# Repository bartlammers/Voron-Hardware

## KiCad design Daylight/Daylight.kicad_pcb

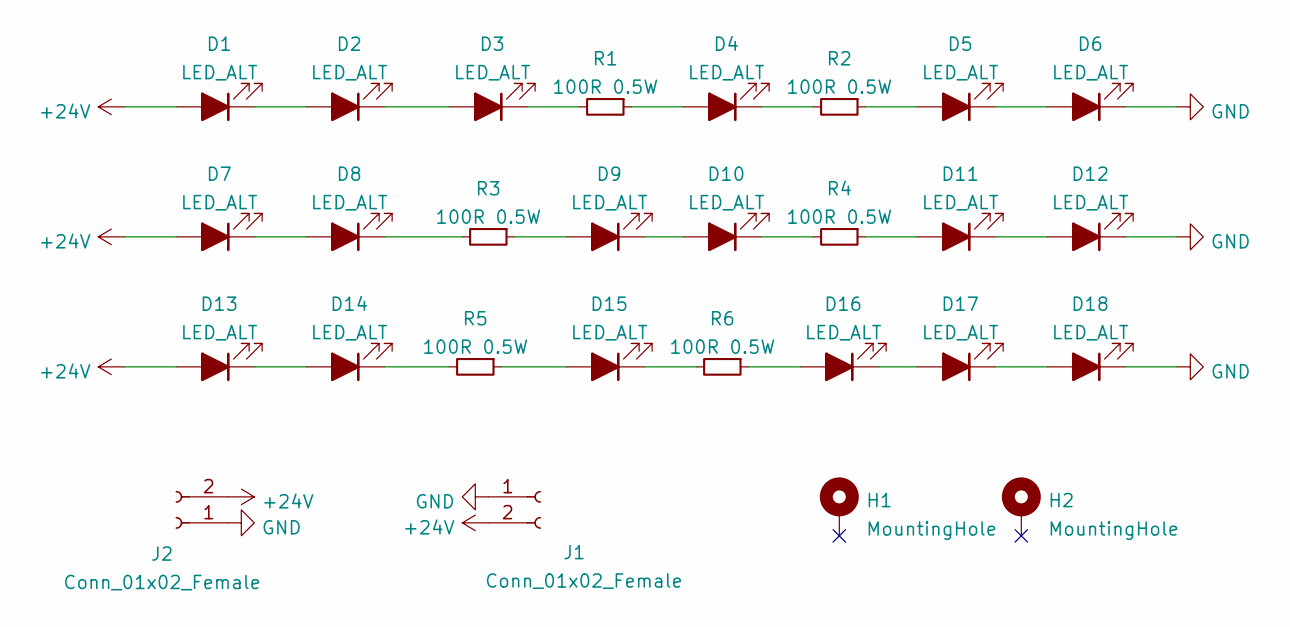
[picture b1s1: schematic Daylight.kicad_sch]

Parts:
D1, D2, D3, D4, D5, D6, D7, D8, D9, D10, D11, D12, D13, D14, D15, D16, D17, D18: LED_ALT; LED_PLCC_2835_Handsoldering_flipped; LCSC C182223
H1, H2: MountingHole; MountingHole_3.2mm_M3_Pad_Via
J1: Conn_01x02_Female; PinHeader_1x02_P2.54mm_Horizontal_mirrored
J2: Conn_01x02_Female; PinHeader_1x02_P2.54mm_Horizontal
R1, R2, R3, R4, R5, R6: 100R 0.5W; R_1210_3225Metric_Pad1.30x2.65mm_HandSolder; LCSC C137089

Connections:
+24V: D1.2 (A), D7.2 (A), D13.2 (A), J1.2, J2.2
GND: D6.1 (K), D12.1 (K), D18.1 (K), J1.1, J2.1
unnamed: D1.1 (K), D2.2 (A)
unnamed: D2.1 (K), D3.2 (A)
unnamed: D3.1 (K), R1.2
unnamed: D4.1 (K), R2.2
unnamed: D4.2 (A), R1.1
unnamed: D5.1 (K), D6.2 (A)
unnamed: D5.2 (A), R2.1
unnamed: D7.1 (K), D8.2 (A)
unnamed: D8.1 (K), R3.2
unnamed: D9.2 (A), R3.1
unnamed: D10.1 (K), R4.2
unnamed: D9.1 (K), D10.2 (A)
unnamed: D11.1 (K), D12.2 (A)
unnamed: D11.2 (A), R4.1
unnamed: D13.1 (K), D14.2 (A)
unnamed: D14.1 (K), R5.2
unnamed: D15.1 (K), R6.2
unnamed: D15.2 (A), R5.1
unnamed: D16.1 (K), D17.2 (A)
unnamed: D16.2 (A), R6.1
unnamed: D17.1 (K), D18.2 (A)

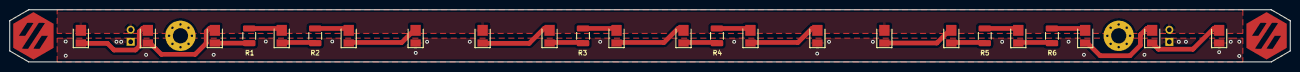
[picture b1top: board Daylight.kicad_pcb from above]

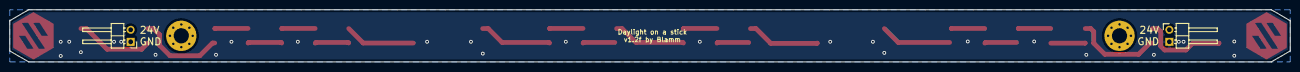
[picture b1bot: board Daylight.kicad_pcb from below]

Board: 2 copper layers, 270.0 x 11.0 mm, 28 parts (2 on the bottom side), 23 nets.

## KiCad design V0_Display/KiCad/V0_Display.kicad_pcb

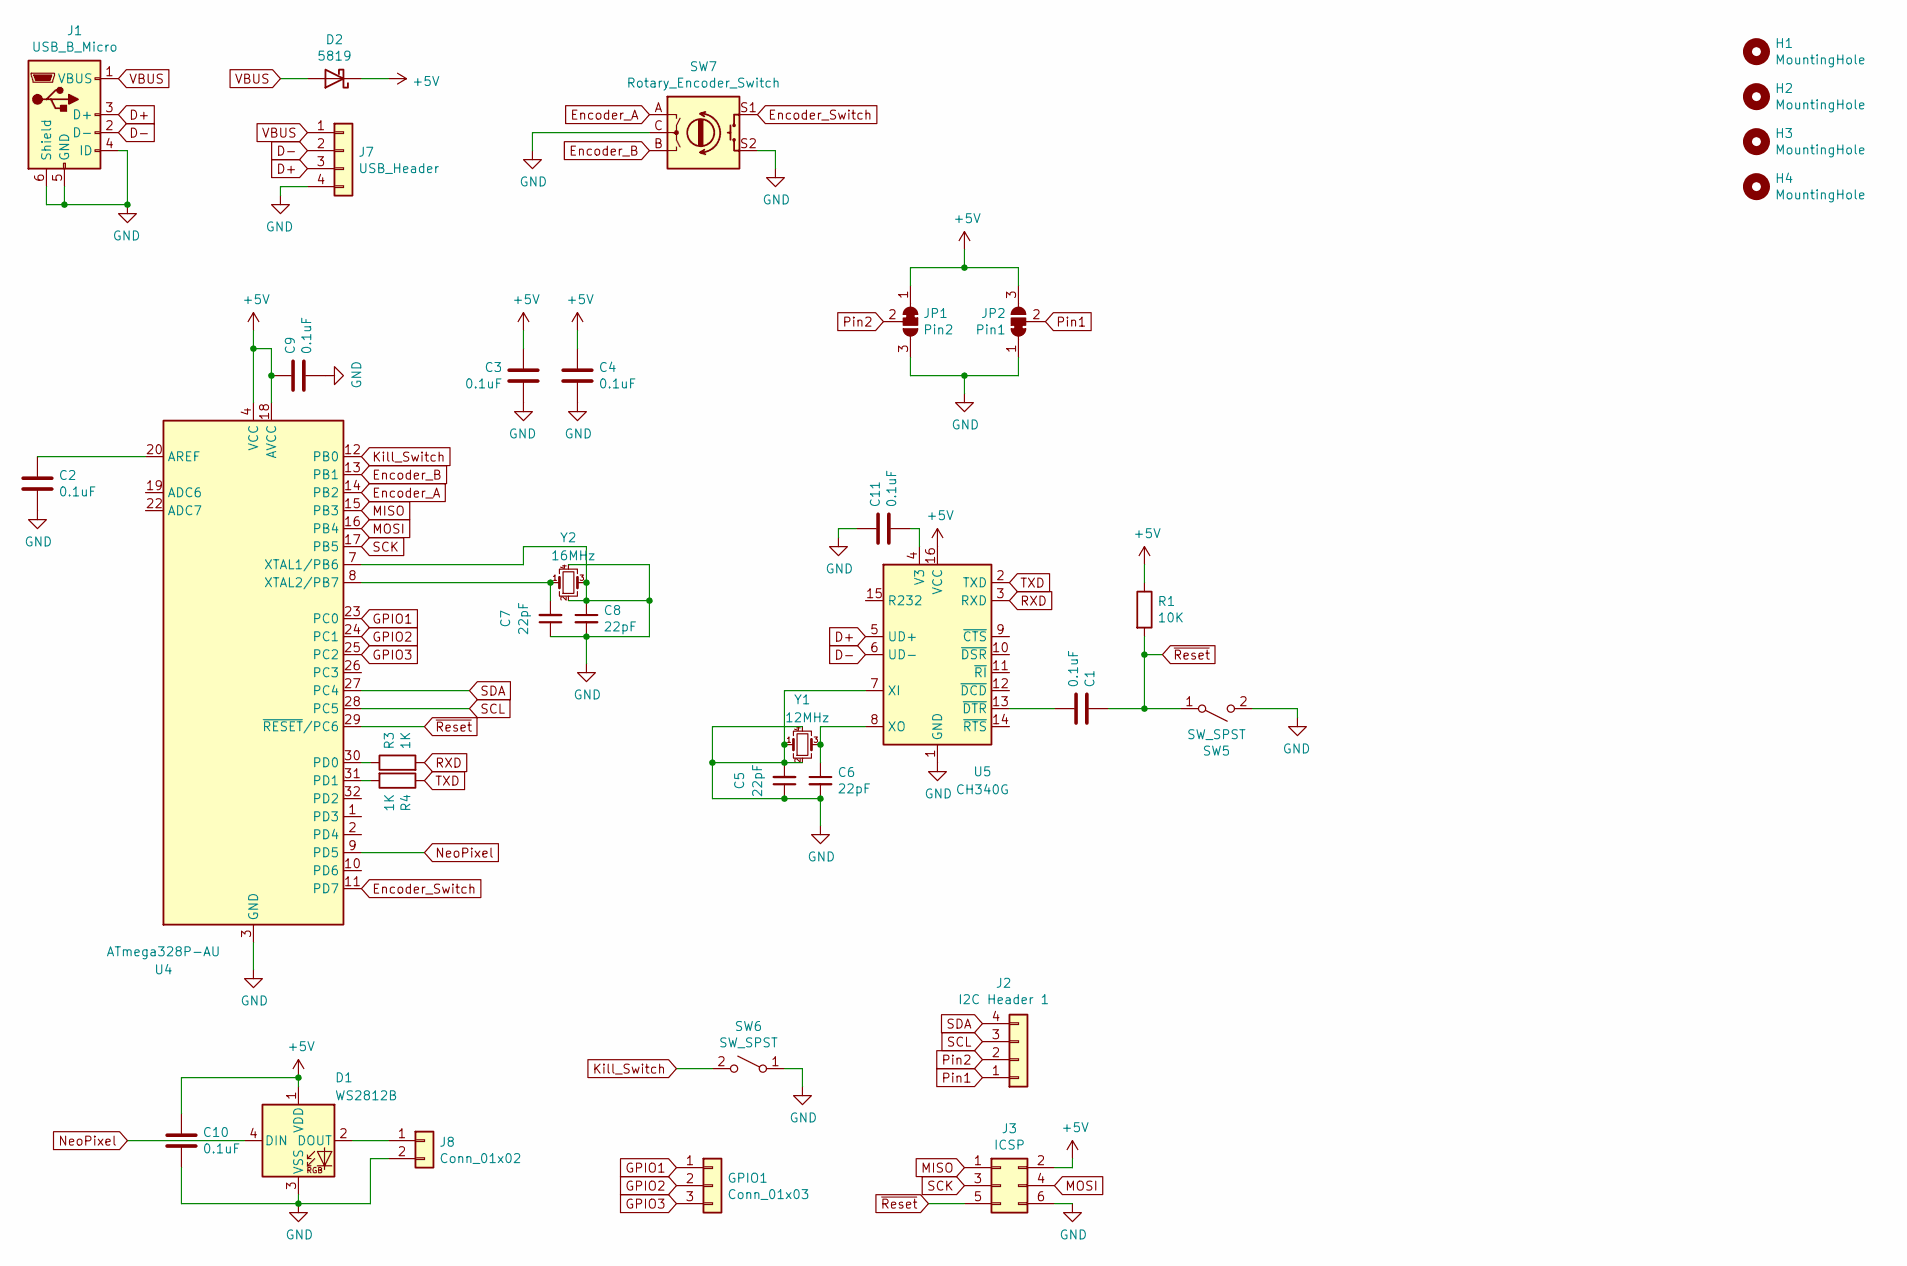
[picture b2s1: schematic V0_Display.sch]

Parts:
C1, C2, C3, C4, C9, C10, C11: 0.1uF; C_0603_1608Metric; LCSC C14663
C5, C6, C7, C8: 22pF; C_0603_1608Metric; LCSC C1653
D1: WS2812B; LED_WS2812B_PLCC4_5.0x5.0mm_P3.2mm
D2: 5819; D_SOD-123; LCSC C8598
GPIO1: Conn_01x03; PinHeader_1x03_P2.54mm_Vertical
H1, H2, H3, H4: MountingHole; MountingHole_3.2mm_M3
J1: USB_B_Micro; MolexVertical&Horizontal_MicroB
J2: I2C Header 1; 1pt3in_OLED
J3: ICSP; PinHeader_2x03_P2.54mm_Vertical
J7: USB_Header; PinHeader_1x04_P2.54mm_Vertical
J8: Conn_01x02; PinHeader_1x02_P2.54mm_Vertical
JP1: Pin2; SolderJumper-3_P1.3mm_Bridged12_Pad1.0x1.5mm
JP2: Pin1; SolderJumper-3_P1.3mm_Bridged12_Pad1.0x1.5mm
R1: 10K; R_0805_2012Metric; LCSC C17414
R3, R4: 1K; R_0805_2012Metric; LCSC C17513
SW5, SW6: SW_SPST; SW_PUSH_6mm
SW7: Rotary_Encoder_Switch; EN11_Encoder
U4: ATmega328P-AU; TQFP-32_7x7mm_P0.8mm; LCSC C14877
U5: CH340G; SOIC-16_3.9x9.9mm_P1.27mm; LCSC C14267
Y1: 12MHz; Crystal_SMD_3225-4Pin_3.2x2.5mm; LCSC C9002
Y2: 16MHz; Crystal_SMD_3225-4Pin_3.2x2.5mm; LCSC C13738

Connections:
+5V: C3.2, C4.1, C9.1, C10.1, D1.1 (VDD), D2.1 (K), J3.2, JP1.1 (A), JP2.3 (B), R1.1, U4.4 (VCC), U4.6 (VCC), U4.18 (AVCC), U5.16 (VCC)
D+: J1.3 (D+), J7.3, U5.5 (UD+)
D-: J1.2 (D-), J7.2, U5.6 (UD-)
Encoder_A: SW7.A, U4.14 (PB2)
Encoder_B: SW7.B, U4.13 (PB1)
Encoder_Switch: SW7.S1, U4.11 (PD7)
GND: C2.2, C3.1, C4.2, C5.1, C5.2, C6.2, C7.1, C8.1, C8.2, C9.2, C10.2, C11.1, D1.3 (VSS), J1.4 (ID), J1.5 (GND), J1.6 (Shield), J3.6, J7.4, J8.2, JP1.3 (B), JP2.1 (A), SW5.2 (B), SW6.1 (A), SW7.C, SW7.S2, U4.3 (GND), U4.5 (GND), U4.7 (XTAL1/PB6), U4.21 (GND), U5.1 (GND), U5.7 (XI), Y1.1, Y1.2, Y1.4, Y2.2, Y2.3, Y2.4
GPIO1: GPIO1.1, U4.23 (PC0)
GPIO2: GPIO1.2, U4.24 (PC1)
GPIO3: GPIO1.3, U4.25 (PC2)
Kill_Switch: SW6.2 (B), U4.12 (PB0)
MISO: J3.1, U4.15 (PB3)
MOSI: J3.4, U4.16 (PB4)
NeoPixel: D1.4 (DIN), U4.9 (PD5)
unnamed: C1.1, U5.13 (~DTR)
unnamed: C2.1, U4.20 (AREF)
unnamed: C6.1, U5.8 (XO), Y1.3
unnamed: C7.2, U4.8 (XTAL2/PB7), Y2.1
unnamed: C11.2, U5.4 (V3)
unnamed: D1.2 (DOUT), J8.1
unnamed: R3.1, U4.30 (PD0)
unnamed: R4.2, U4.31 (PD1)
Pin1: J2.1, JP2.2 (C)
Pin2: J2.2, JP1.2 (C)
RXD: R3.2, U5.3 (RXD)
SCK: J3.3, U4.17 (PB5)
SCL: J2.3, U4.28 (PC5)
SDA: J2.4, U4.27 (PC4)
TXD: R4.1, U5.2 (TXD)
VBUS: D2.2 (A), J1.1 (VBUS), J7.1
~Reset: C1.2, J3.5, R1.2, SW5.1 (A), U4.29 (~RESET~/PC6)

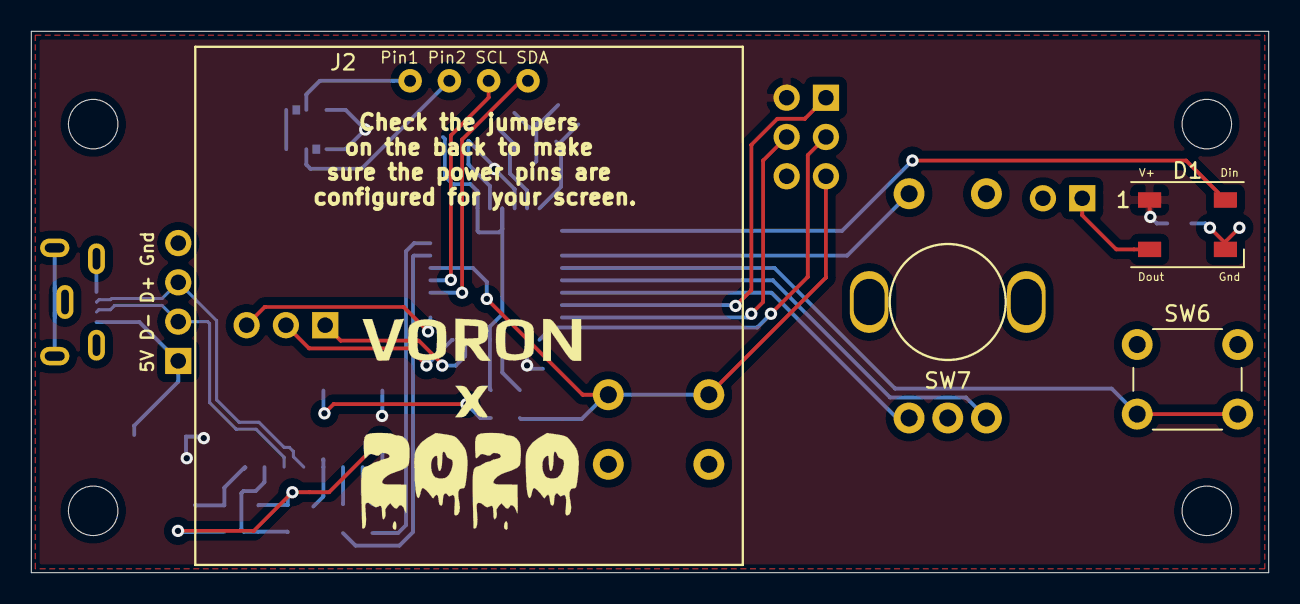
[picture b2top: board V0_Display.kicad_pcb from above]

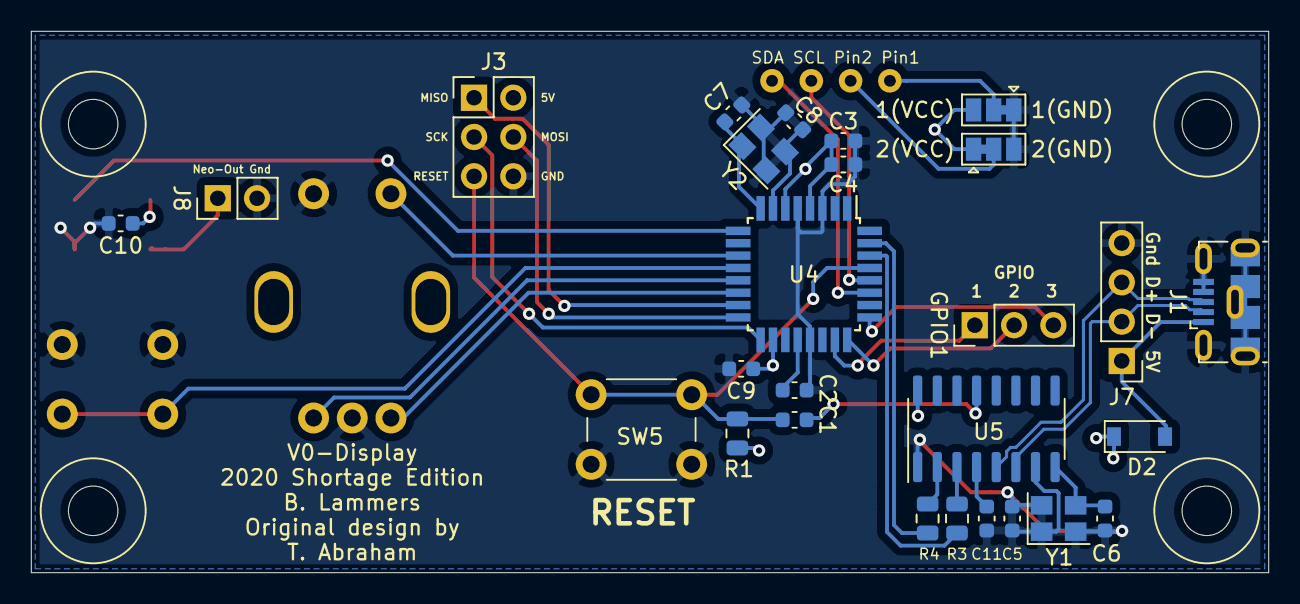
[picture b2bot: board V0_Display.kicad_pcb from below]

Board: 2 copper layers, 80.0 x 35.0 mm, 35 parts (27 on the bottom side), 31 nets.

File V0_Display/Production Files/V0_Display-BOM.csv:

Comment,Designator,Footprint,LCSC Part #
0.1uF Unpolarized capacitor,"C1,C2,C3,C4,C9,C10,C11",C_0603_1608Metric,C14663
"22pF Unpolarized capacitor, small symbol","C5,C6,C7,C8",C_0603_1608Metric,C1653
WS2812B RGB LED with integrated controller,D1,LED_WS2812B_PLCC4_5.0x5.0mm_P3.2mm,
5819 Schottky diode,D2,D_SOD-123,C8598
"Conn_01x03 Generic connector, single row, 01x03, script generated (kicad-library-utils/schlib/autogen/connector/)",GPIO1,PinHeader_1x03_P2.54mm_Vertical,
MountingHole Mounting Hole without connection,"H1,H2,H3,H4",MountingHole_3.2mm_M3,
USB_B_Micro USB Micro Type B connector,J1,MolexVertical&Horizontal_MicroB,
"I2C Header 1 Generic connector, single row, 01x04, script generated (kicad-library-utils/schlib/autogen/connector/)",J2,1pt3in_OLED,
"ICSP Generic connector, double row, 02x03, odd/even pin numbering scheme (row 1 odd numbers, row 2 even numbers), script generated (kicad-library-utils/schlib/autogen/connector/)",J3,PinHeader_2x03_P2.54mm_Vertical,
"USB_Header Generic connector, single row, 01x04, script generated (kicad-library-utils/schlib/autogen/connector/)",J7,PinHeader_1x04_P2.54mm_Vertical,
"Conn_01x02 Generic connector, single row, 01x02, script generated (kicad-library-utils/schlib/autogen/connector/)",J8,PinHeader_1x02_P2.54mm_Vertical,
"Pin2 3-pole Solder Jumper, pins 1+2 closed/bridged",JP1,SolderJumper-3_P1.3mm_Bridged12_Pad1.0x1.5mm,
"Pin1 3-pole Solder Jumper, pins 1+2 closed/bridged",JP2,SolderJumper-3_P1.3mm_Bridged12_Pad1.0x1.5mm,
10K Resistor,R1,R_0805_2012Metric,C17414
1K Resistor,"R3,R4",R_0805_2012Metric,C17513
SW_SPST Single Pole Single Throw (SPST) switch,"SW5,SW6",SW_PUSH_6mm,
"Rotary_Encoder_Switch Rotary encoder, dual channel, incremental quadrate outputs, with switch",SW7,EN11_Encoder,
"ATmega328P-AU 20MHz, 32kB Flash, 2kB SRAM, 1kB EEPROM, TQFP-32",U4,TQFP-32_7x7mm_P0.8mm,C14877
"CH340G USB serial converter, UART, SOIC-16",U5,SOIC-16_3.9x9.9mm_P1.27mm,C14267
"12MHz Four pin crystal, GND on pins 2 and 4, small symbol",Y1,Crystal_SMD_3225-4Pin_3.2x2.5mm,C9002
"16MHz Four pin crystal, GND on pins 2 and 4, small symbol",Y2,Crystal_SMD_3225-4Pin_3.2x2.5mm,C13738

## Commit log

2021-05-05 Create Atmega328p version of the V0 Display
2022-05-19 Flipped leds for DFH
